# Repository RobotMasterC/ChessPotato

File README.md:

# ChessPotato

An XIAO RP2040 6 Key Macro pad with a Rotary Encoder that uses KMK for firmware

## BOM
- 6x DSA keycaps
- 6x Cherry MX Switches
- 1x XIAO RP2040
- 1x EC11 Rotary Encoder
- 4x M3x16 Bolt
- 4x M3 Heatset

## Pad Image

## Schematic

## PCB

## CAD

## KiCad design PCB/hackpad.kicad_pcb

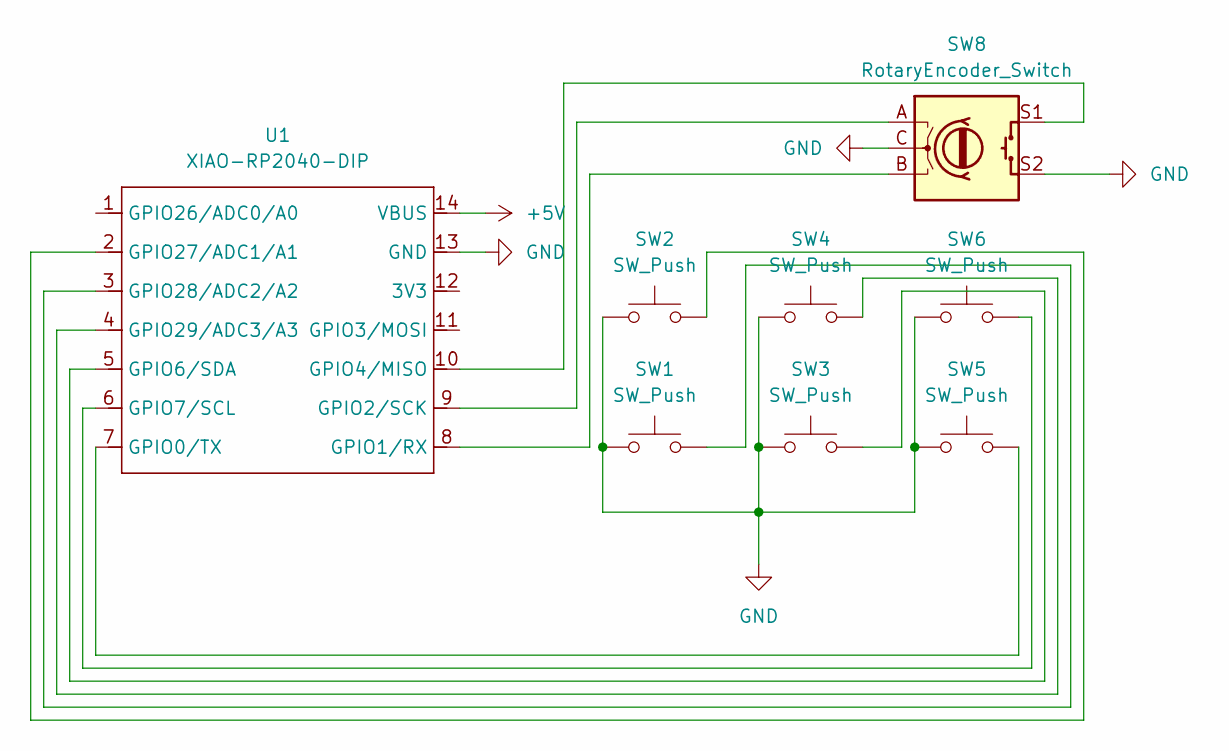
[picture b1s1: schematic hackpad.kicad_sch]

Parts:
SW1, SW2, SW3, SW4, SW5, SW6: SW_Push; SW_Cherry_MX_1.00u_PCB
SW8: RotaryEncoder_Switch; RotaryEncoder_Alps_EC11E-Switch_Vertical_H20mm
U1: XIAO-RP2040-DIP

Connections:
+5V: U1.14 (VBUS)
GND: SW1.1, SW2.1, SW3.1, SW4.1, SW5.1, SW6.1, SW8.C, SW8.S2, U1.13 (GND)
unnamed: SW5.2, U1.7 (GPIO0/TX)
unnamed: SW8.B, U1.8 (GPIO1/RX)
unnamed: SW8.A, U1.9 (GPIO2/SCK)
unnamed: SW8.S1, U1.10 (GPIO4/MISO)
unnamed: SW3.2, U1.5 (GPIO6/SDA)
unnamed: SW6.2, U1.6 (GPIO7/SCL)
unnamed: SW2.2, U1.2 (GPIO27/ADC1/A1)
unnamed: SW1.2, U1.3 (GPIO28/ADC2/A2)
unnamed: SW4.2, U1.4 (GPIO29/ADC3/A3)

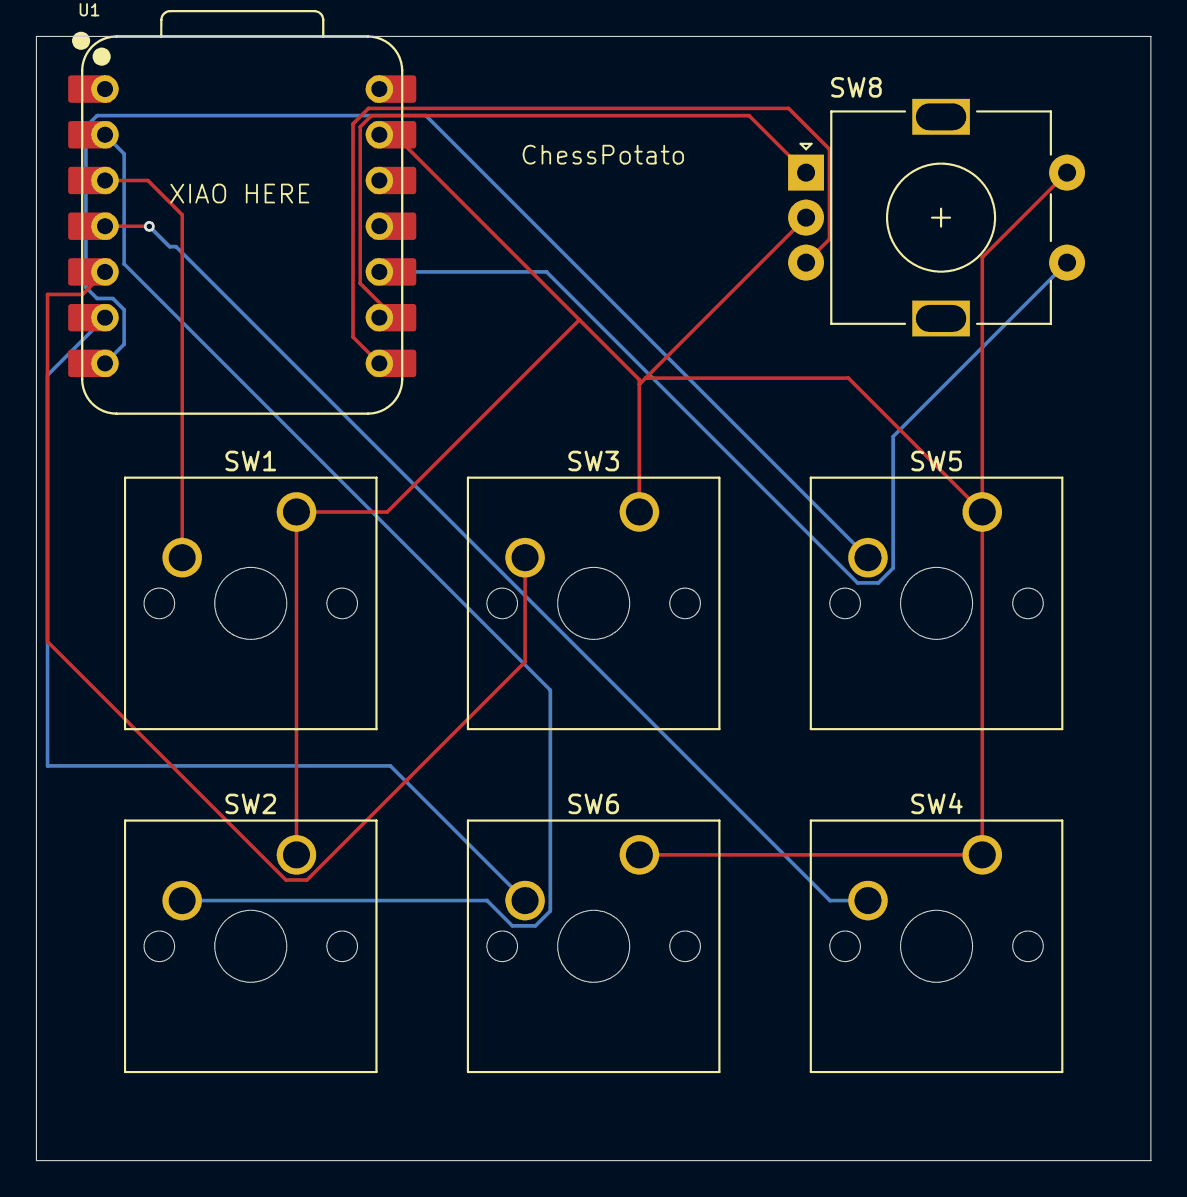
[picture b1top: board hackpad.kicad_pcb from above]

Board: 2 copper layers, 61.9 x 62.5 mm, 8 parts (0 on the bottom side), 10 nets.

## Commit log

2025-05-31 Create Firmware Folder
2025-05-31 Create CAD Folder
2025-05-31 Create PCB Folder
